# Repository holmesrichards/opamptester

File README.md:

# Op amp tester

This is a stoopid little op amp tester. This circuit does not do any quantitative tests — you would not use it to determine if an op amp is fake. It just checks basic functionality: Does it amplify a small signal? Put an op amp in one of the sockets, connect power, push the button. If the LEDs light up (all four for quad op amps, two for duals, one for singles) it passes.

This is based on a [blog post](https://tangentsoft.net/elec/opamp-tester.html) by Warren Young. Since I have a bench supply usually set up for ±12 V I got rid of the rail splitter and changed the voltage divider accordingly.

I quadrupled the rest of the circuit to test quad op amps. Then I added sockets for single and dual op amps. The pins on these are just connected to the quad socket, so only one socket should be populated at a time.

I changed the LED resistors to 620R because I can imagine a failure mode in which the op amp puts out +12 V. This will limit LED current to 16.8 mV assuming a forward voltage of 1.6 V. For LEDs with different forward voltage or current limit, adjust these resistors accordingly.

I also added a switch to ground the input, because a good op amp not only should light up the LED when the input is present, it should *not* light it up when the input is absent.

## Build notes

I was out of 13k and 15k resistors when I built this so substituted:

* 12k for 13k
* 11k for 12k
* 12k for 15k
* 1.8k for 2.2k

which works fine.

The Degson pluggable terminal block is what I have on my bench supply wires. Change it if you need to.

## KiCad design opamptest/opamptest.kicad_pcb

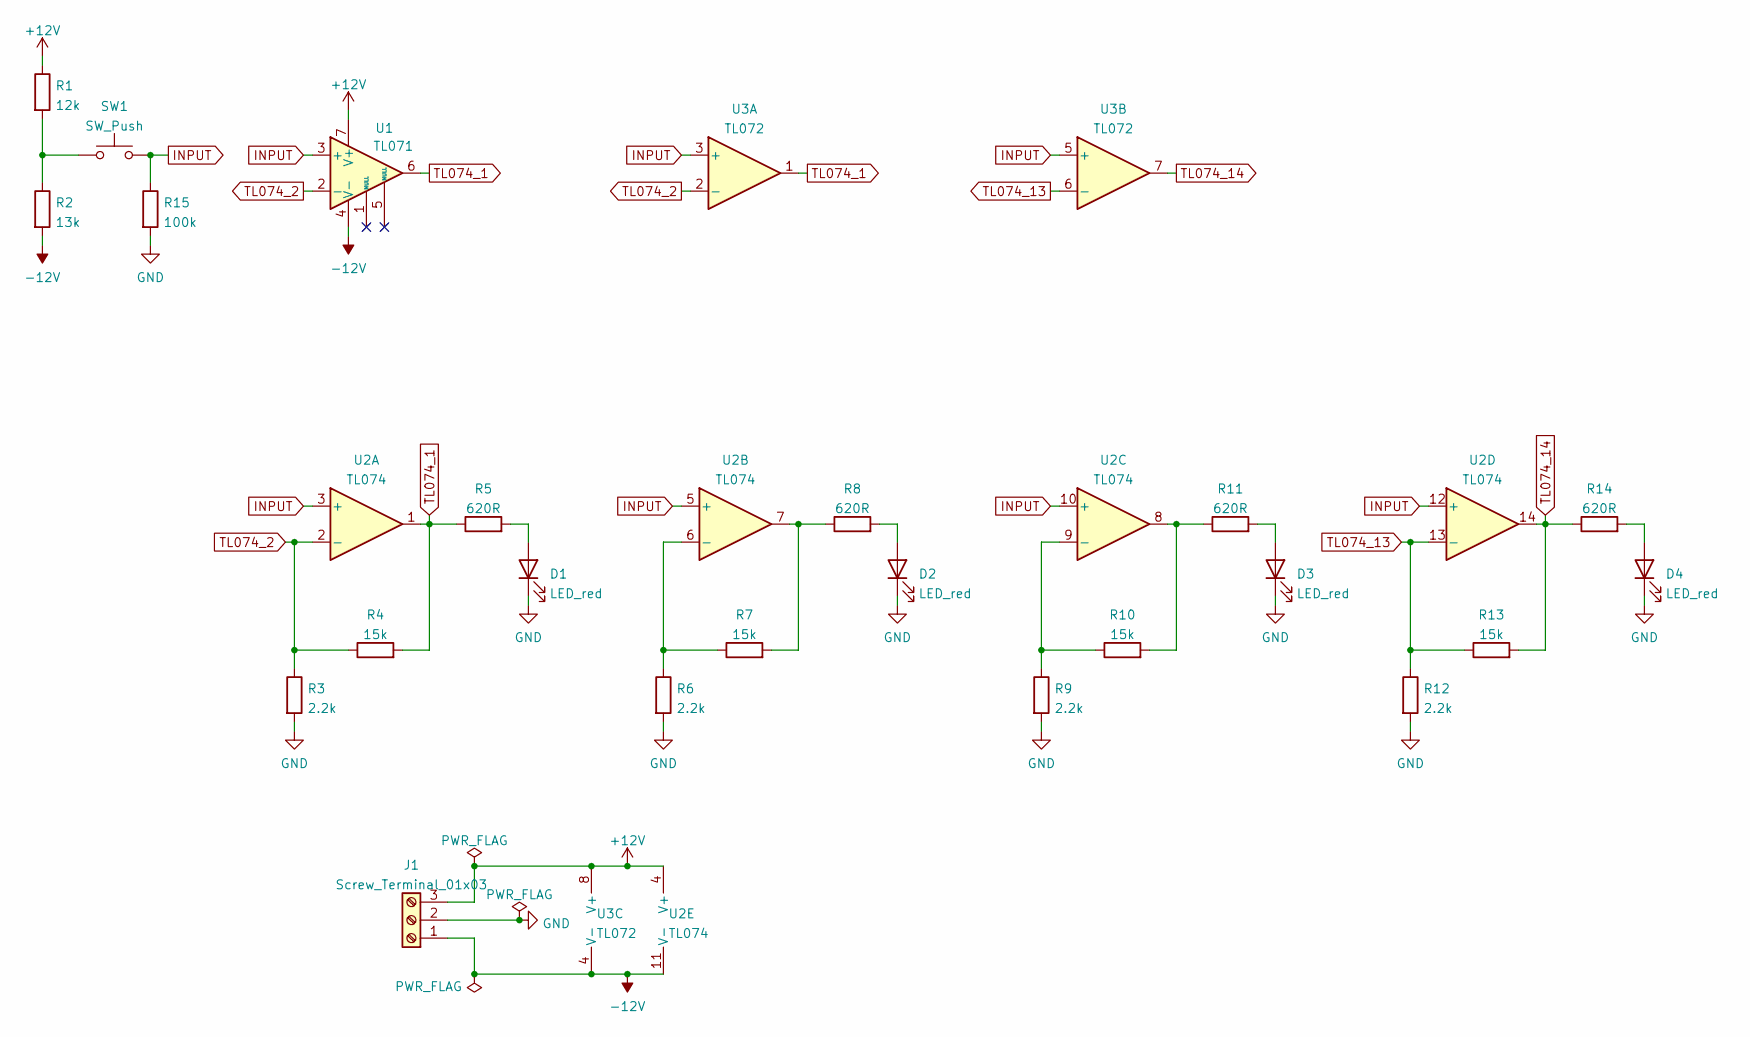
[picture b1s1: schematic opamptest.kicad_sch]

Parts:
D1, D2, D3, D4: LED_red; LED_D3.0mm
J1: Screw_Terminal_01x03; TerminalBlock_dinkle_pluggable_3_P5.00mm; Part DG301
R1: 12k; R_Axial_DIN0207_L6.3mm_D2.5mm_P10.16mm_Horizontal
R2: 13k; R_Axial_DIN0207_L6.3mm_D2.5mm_P10.16mm_Horizontal
R3, R6, R9, R12: 2.2k; R_Axial_DIN0207_L6.3mm_D2.5mm_P10.16mm_Horizontal
R4, R7, R10, R13: 15k; R_Axial_DIN0207_L6.3mm_D2.5mm_P10.16mm_Horizontal
R5, R8, R11, R14: 620R; R_Axial_DIN0207_L6.3mm_D2.5mm_P10.16mm_Horizontal
R15: 100k; R_Axial_DIN0207_L6.3mm_D2.5mm_P10.16mm_Horizontal
SW1: SW_Push; SW_PUSH_6mm
U1: TL071; DIP-8_W7.62mm_Socket_LongPads
U2: TL074; DIP-14_W7.62mm_Socket_LongPads
U3: TL072; DIP-8_W7.62mm_Socket_LongPads

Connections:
+12V: J1.3, R1.1, U1.7 (V+), U2.4 (V+), U3.8 (V+)
-12V: J1.1, R2.2, U1.4 (V-), U2.11 (V-), U3.4 (V-)
GND: D1.1 (K), D2.1 (K), D3.1 (K), D4.1 (K), J1.2, R3.2, R6.2, R9.2, R12.2, R15.2
INPUT: R15.1, SW1.2, U1.3 (+), U2.3 (+), U2.5 (+), U2.10 (+), U2.12 (+), U3.3 (+), U3.5 (+)
unnamed: D1.2 (A), R5.2
unnamed: D2.2 (A), R8.2
unnamed: D3.2 (A), R11.2
unnamed: D4.2 (A), R14.2
unnamed: R1.2, R2.1, SW1.1
unnamed: R6.1, R7.1, U2.6 (-)
unnamed: R7.2, R8.1, U2.7
unnamed: R9.1, R10.1, U2.9 (-)
unnamed: R10.2, R11.1, U2.8
TL074_1: R4.2, R5.1, U1.6, U2.1, U3.1
TL074_2: R3.1, R4.1, U1.2 (-), U2.2 (-), U3.2 (-)
TL074_13: R12.1, R13.1, U2.13 (-), U3.6 (-)
TL074_14: R13.2, R14.1, U2.14, U3.7

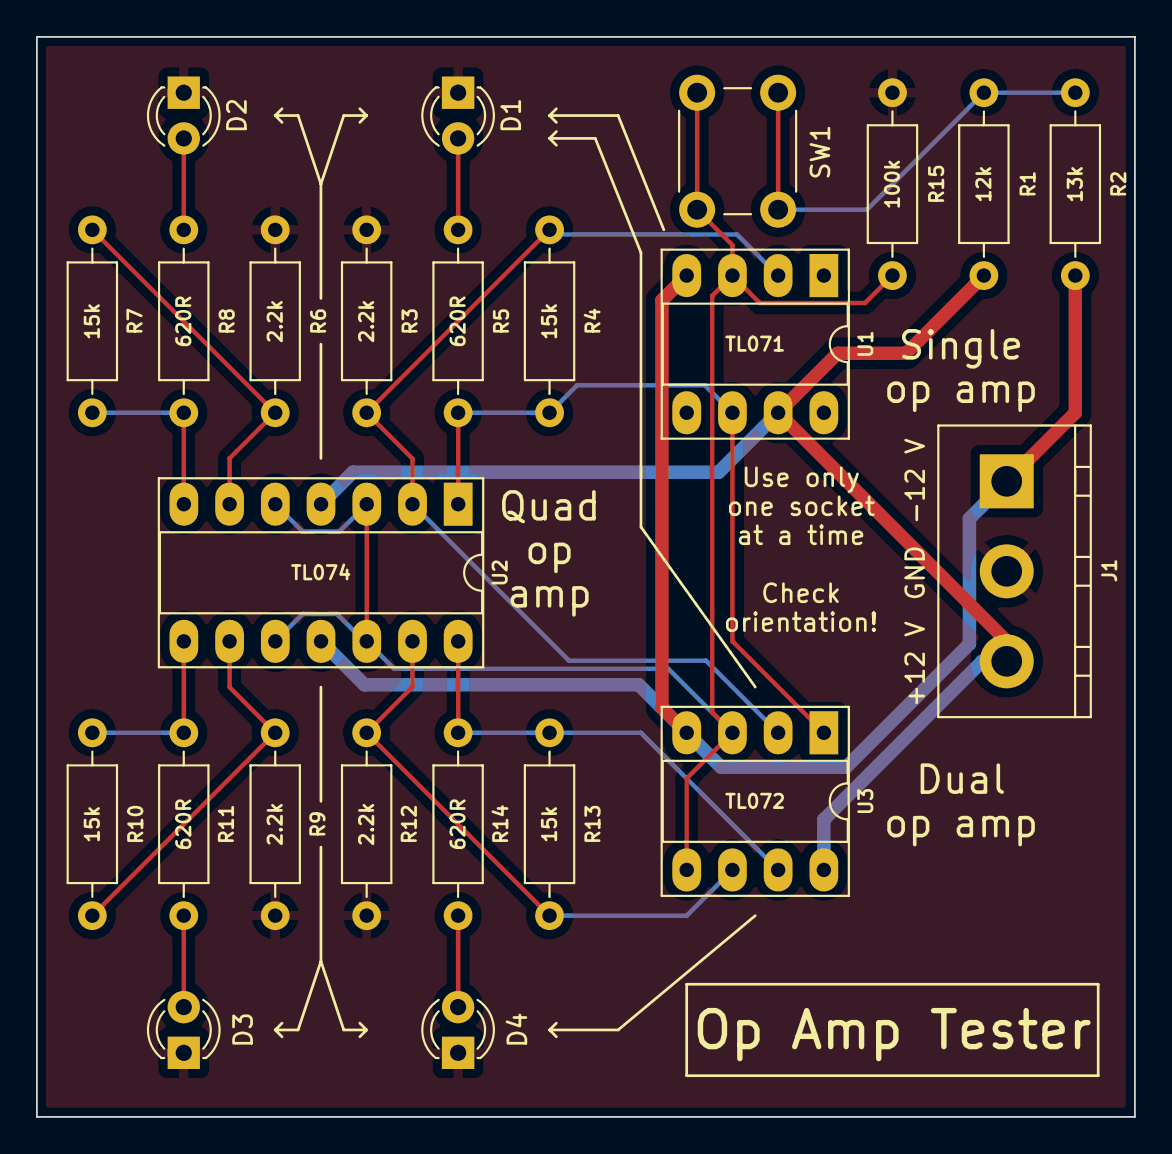
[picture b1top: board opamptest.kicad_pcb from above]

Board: 2 copper layers, 61.0 x 60.0 mm, 24 parts (0 on the bottom side), 17 nets.

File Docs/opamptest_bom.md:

# opamptest.kicad_sch BOM

Thu 14 Apr 2022 06:17:21 PM EDT

Generated from schematic by Eeschema 6.0.4-6f826c9f35~116~ubuntu20.04.1

**Component Count:** 24

| Refs | Qty | Component | Description | Manufacturer | Part | Vendor | SKU |
| ----- | --- | ---- | ----------- | ---- | ---- | ---- | ---- |
| D1, D2, D3, D4 | 4 | LED_red | Light emitting diode |  |  | Tayda | A-1554 |
| J1 | 1 | Screw_Terminal_01x03 | Screw terminal | Degson | DG301 | Tayda | A-669 |
| R1 | 1 | 12k | Resistor |  |  | Tayda |  |
| R2 | 1 | 13k | Resistor |  |  | Tayda |  |
| R3, R6, R9, R12 | 4 | 2.2k | Resistor |  |  | Tayda |  |
| R4, R7, R10, R13 | 4 | 15k | Resistor |  |  | Tayda |  |
| R5, R8, R11, R14 | 4 | 620R | Resistor |  |  | Tayda |  |
| R15 | 1 | 100k | Resistor |  |  | Tayda |  |
| SW1 | 1 | SW_Push | Push button tactile switch |  |  |  |  |
| | 2 | | 8 pin DIP socket | | | | |
| | 1 | | 14 pin DIP socket | | | | |

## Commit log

2022-04-14 Initial version
2022-04-14 Create LICENSE
